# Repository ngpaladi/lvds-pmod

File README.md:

# lvds-pmod
LVDS adapter for PMOD

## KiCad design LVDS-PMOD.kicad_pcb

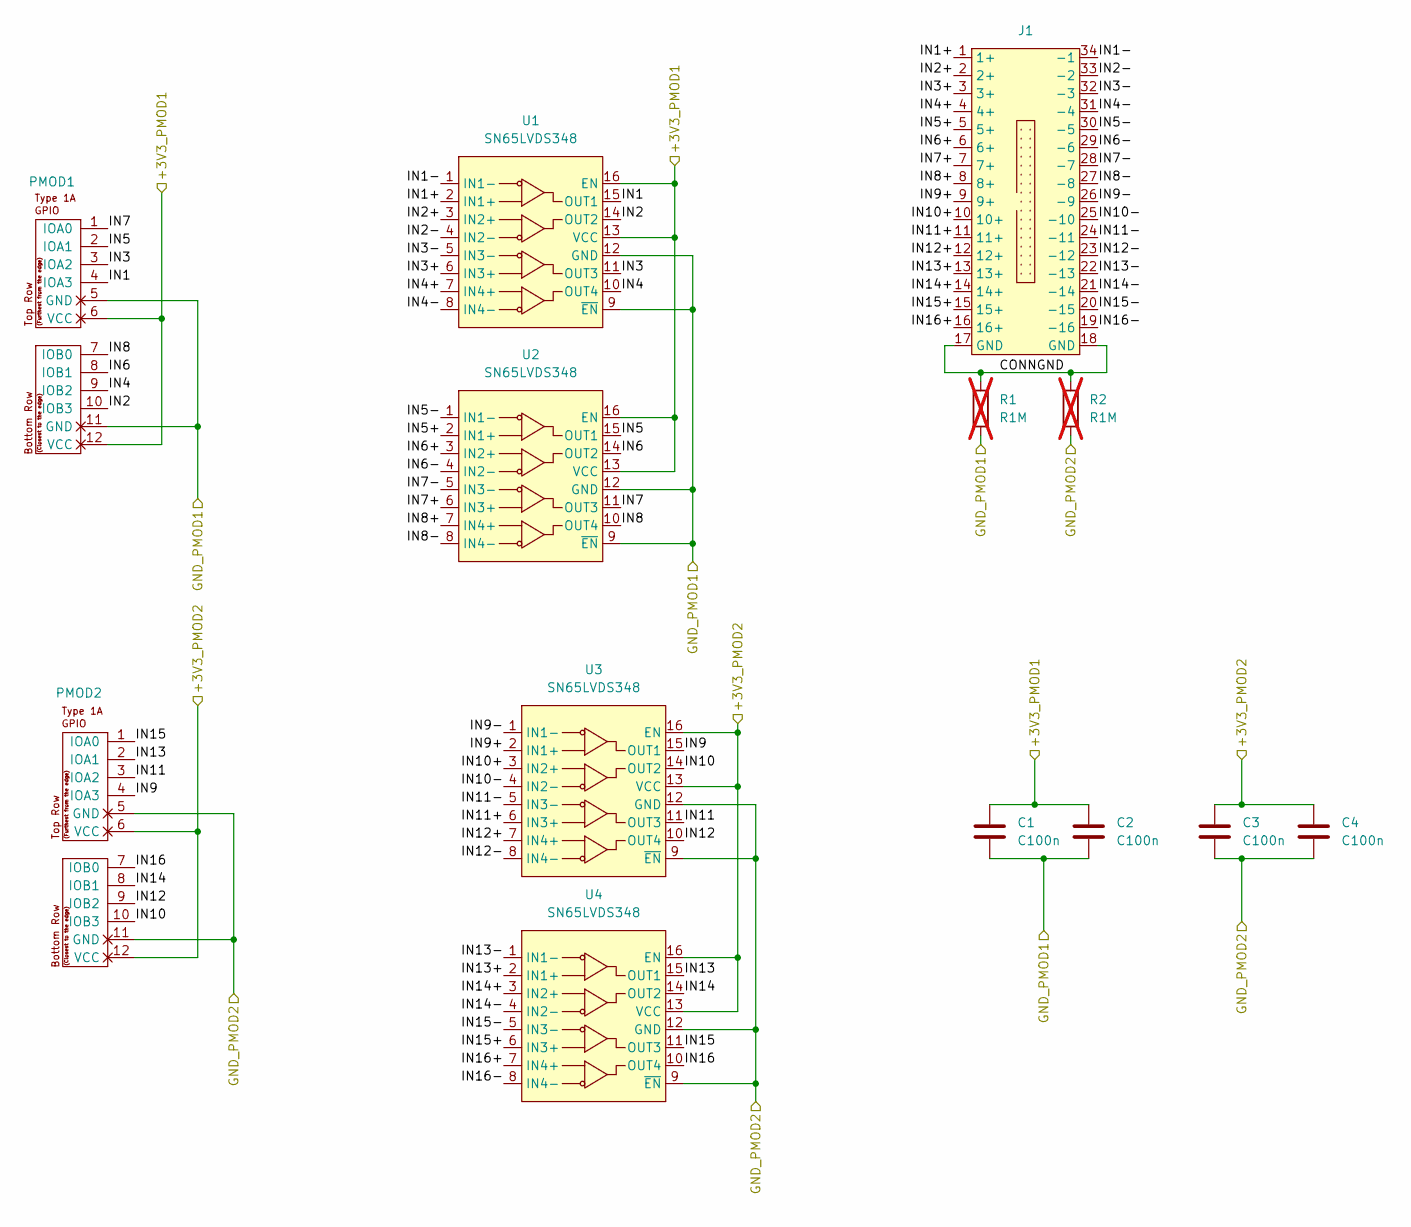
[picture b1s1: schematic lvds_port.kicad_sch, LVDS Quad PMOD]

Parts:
C1, C2, C3, C4: C100n; C_0402_1005Metric_Pad0.74x0.62mm_HandSolder
J1: 302-S341; LVDS_Connector
PMOD1, PMOD2: PMOD-Device-x2-Type-1A-GPIO; pmod_pin_array_6x2
R1, R2: R1M; R_1206_3216Metric_Pad1.30x1.75mm_HandSolder; not fitted
U1, U2, U3, U4: SN65LVDS348; SOIC-16_3.9x9.9mm_P1.27mm

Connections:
+3V3A: C1.1, C2.1, PMOD1.6 (VCC), PMOD1.12 (VCC), U1.13 (VCC), U1.16 (EN), U2.13 (VCC), U2.16 (EN)
+3V3B: C3.1, C4.1, PMOD2.6 (VCC), PMOD2.12 (VCC), U3.13 (VCC), U3.16 (EN), U4.13 (VCC), U4.16 (EN)
/LVDS Port AB/CONNGND: J1.17 (GND), J1.18 (GND), R1.1, R2.1
/LVDS Port AB/IN1: PMOD1.4 (IOA3), U1.15 (OUT1)
/LVDS Port AB/IN1+: J1.1 (1+), U1.2 (IN1+)
/LVDS Port AB/IN1-: J1.34 (-1), U1.1 (IN1-)
/LVDS Port AB/IN2: PMOD1.10 (IOB3), U1.14 (OUT2)
/LVDS Port AB/IN2+: J1.2 (2+), U1.3 (IN2+)
/LVDS Port AB/IN2-: J1.33 (-2), U1.4 (IN2-)
/LVDS Port AB/IN3: PMOD1.3 (IOA2), U1.11 (OUT3)
/LVDS Port AB/IN3+: J1.3 (3+), U1.6 (IN3+)
/LVDS Port AB/IN3-: J1.32 (-3), U1.5 (IN3-)
/LVDS Port AB/IN4: PMOD1.9 (IOB2), U1.10 (OUT4)
/LVDS Port AB/IN4+: J1.4 (4+), U1.7 (IN4+)
/LVDS Port AB/IN4-: J1.31 (-4), U1.8 (IN4-)
/LVDS Port AB/IN5: PMOD1.2 (IOA1), U2.15 (OUT1)
/LVDS Port AB/IN5+: J1.5 (5+), U2.2 (IN1+)
/LVDS Port AB/IN5-: J1.30 (-5), U2.1 (IN1-)
/LVDS Port AB/IN6: PMOD1.8 (IOB1), U2.14 (OUT2)
/LVDS Port AB/IN6+: J1.6 (6+), U2.3 (IN2+)
/LVDS Port AB/IN6-: J1.29 (-6), U2.4 (IN2-)
/LVDS Port AB/IN7: PMOD1.1 (IOA0), U2.11 (OUT3)
/LVDS Port AB/IN7+: J1.7 (7+), U2.6 (IN3+)
/LVDS Port AB/IN7-: J1.28 (-7), U2.5 (IN3-)
/LVDS Port AB/IN8: PMOD1.7 (IOB0), U2.10 (OUT4)
/LVDS Port AB/IN8+: J1.8 (8+), U2.7 (IN4+)
/LVDS Port AB/IN8-: J1.27 (-8), U2.8 (IN4-)
/LVDS Port AB/IN9: PMOD2.4 (IOA3), U3.15 (OUT1)
/LVDS Port AB/IN9+: J1.9 (9+), U3.2 (IN1+)
/LVDS Port AB/IN9-: J1.26 (-9), U3.1 (IN1-)
/LVDS Port AB/IN10: PMOD2.10 (IOB3), U3.14 (OUT2)
/LVDS Port AB/IN10+: J1.10 (10+), U3.3 (IN2+)
/LVDS Port AB/IN10-: J1.25 (-10), U3.4 (IN2-)
/LVDS Port AB/IN11: PMOD2.3 (IOA2), U3.11 (OUT3)
/LVDS Port AB/IN11+: J1.11 (11+), U3.6 (IN3+)
/LVDS Port AB/IN11-: J1.24 (-11), U3.5 (IN3-)
/LVDS Port AB/IN12: PMOD2.9 (IOB2), U3.10 (OUT4)
/LVDS Port AB/IN12+: J1.12 (12+), U3.7 (IN4+)
/LVDS Port AB/IN12-: J1.23 (-12), U3.8 (IN4-)
/LVDS Port AB/IN13: PMOD2.2 (IOA1), U4.15 (OUT1)
/LVDS Port AB/IN13+: J1.13 (13+), U4.2 (IN1+)
/LVDS Port AB/IN13-: J1.22 (-13), U4.1 (IN1-)
/LVDS Port AB/IN14: PMOD2.8 (IOB1), U4.14 (OUT2)
/LVDS Port AB/IN14+: J1.14 (14+), U4.3 (IN2+)
/LVDS Port AB/IN14-: J1.21 (-14), U4.4 (IN2-)
/LVDS Port AB/IN15: PMOD2.1 (IOA0), U4.11 (OUT3)
/LVDS Port AB/IN15+: J1.15 (15+), U4.6 (IN3+)
/LVDS Port AB/IN15-: J1.20 (-15), U4.5 (IN3-)
/LVDS Port AB/IN16: PMOD2.7 (IOB0), U4.10 (OUT4)
/LVDS Port AB/IN16+: J1.16 (16+), U4.7 (IN4+)
/LVDS Port AB/IN16-: J1.19 (-16), U4.8 (IN4-)
GND: C1.2, C2.2, C3.2, C4.2, PMOD1.5 (GND), PMOD1.11 (GND), PMOD2.5 (GND), PMOD2.11 (GND), R1.2, R2.2, U1.9 (~EN), U1.12 (GND), U2.9 (~EN), U2.12 (GND), U3.9 (~EN), U3.12 (GND), U4.9 (~EN), U4.12 (GND); also elsewhere on the board

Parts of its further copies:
C5, C6, C7, C8: C100n; C_0402_1005Metric_Pad0.74x0.62mm_HandSolder
J2: 302-S341; LVDS_Connector
PMOD3, PMOD4: PMOD-Device-x2-Type-1A-GPIO; pmod_pin_array_6x2
R3, R4: R1M; R_1206_3216Metric_Pad1.30x1.75mm_HandSolder; not fitted
U5, U6, U7, U8: SN65LVDS348; SOIC-16_3.9x9.9mm_P1.27mm

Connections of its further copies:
+3V3C: C5.1, C6.1, PMOD3.6 (VCC), PMOD3.12 (VCC), U5.13 (VCC), U5.16 (EN), U6.13 (VCC), U6.16 (EN)
+3V3D: C7.1, C8.1, PMOD4.6 (VCC), PMOD4.12 (VCC), U7.13 (VCC), U7.16 (EN), U8.13 (VCC), U8.16 (EN)
/LVDS Port CD/CONNGND: J2.17 (GND), J2.18 (GND), R3.1, R4.1
/LVDS Port CD/IN1: PMOD3.4 (IOA3), U5.15 (OUT1)
/LVDS Port CD/IN1+: J2.1 (1+), U5.2 (IN1+)
/LVDS Port CD/IN1-: J2.34 (-1), U5.1 (IN1-)
/LVDS Port CD/IN2: PMOD3.10 (IOB3), U5.14 (OUT2)
/LVDS Port CD/IN2+: J2.2 (2+), U5.3 (IN2+)
/LVDS Port CD/IN2-: J2.33 (-2), U5.4 (IN2-)
/LVDS Port CD/IN3: PMOD3.3 (IOA2), U5.11 (OUT3)
/LVDS Port CD/IN3+: J2.3 (3+), U5.6 (IN3+)
/LVDS Port CD/IN3-: J2.32 (-3), U5.5 (IN3-)
/LVDS Port CD/IN4: PMOD3.9 (IOB2), U5.10 (OUT4)
/LVDS Port CD/IN4+: J2.4 (4+), U5.7 (IN4+)
/LVDS Port CD/IN4-: J2.31 (-4), U5.8 (IN4-)
/LVDS Port CD/IN5: PMOD3.2 (IOA1), U6.15 (OUT1)
/LVDS Port CD/IN5+: J2.5 (5+), U6.2 (IN1+)
/LVDS Port CD/IN5-: J2.30 (-5), U6.1 (IN1-)
/LVDS Port CD/IN6: PMOD3.8 (IOB1), U6.14 (OUT2)
/LVDS Port CD/IN6+: J2.6 (6+), U6.3 (IN2+)
/LVDS Port CD/IN6-: J2.29 (-6), U6.4 (IN2-)
/LVDS Port CD/IN7: PMOD3.1 (IOA0), U6.11 (OUT3)
/LVDS Port CD/IN7+: J2.7 (7+), U6.6 (IN3+)
/LVDS Port CD/IN7-: J2.28 (-7), U6.5 (IN3-)
/LVDS Port CD/IN8: PMOD3.7 (IOB0), U6.10 (OUT4)
/LVDS Port CD/IN8+: J2.8 (8+), U6.7 (IN4+)
/LVDS Port CD/IN8-: J2.27 (-8), U6.8 (IN4-)
/LVDS Port CD/IN9: PMOD4.4 (IOA3), U7.15 (OUT1)
/LVDS Port CD/IN9+: J2.9 (9+), U7.2 (IN1+)
/LVDS Port CD/IN9-: J2.26 (-9), U7.1 (IN1-)
/LVDS Port CD/IN10: PMOD4.10 (IOB3), U7.14 (OUT2)
/LVDS Port CD/IN10+: J2.10 (10+), U7.3 (IN2+)
/LVDS Port CD/IN10-: J2.25 (-10), U7.4 (IN2-)
/LVDS Port CD/IN11: PMOD4.3 (IOA2), U7.11 (OUT3)
/LVDS Port CD/IN11+: J2.11 (11+), U7.6 (IN3+)
/LVDS Port CD/IN11-: J2.24 (-11), U7.5 (IN3-)
/LVDS Port CD/IN12: PMOD4.9 (IOB2), U7.10 (OUT4)
/LVDS Port CD/IN12+: J2.12 (12+), U7.7 (IN4+)
/LVDS Port CD/IN12-: J2.23 (-12), U7.8 (IN4-)
/LVDS Port CD/IN13: PMOD4.2 (IOA1), U8.15 (OUT1)
/LVDS Port CD/IN13+: J2.13 (13+), U8.2 (IN1+)
/LVDS Port CD/IN13-: J2.22 (-13), U8.1 (IN1-)
/LVDS Port CD/IN14: PMOD4.8 (IOB1), U8.14 (OUT2)
/LVDS Port CD/IN14+: J2.14 (14+), U8.3 (IN2+)
/LVDS Port CD/IN14-: J2.21 (-14), U8.4 (IN2-)
/LVDS Port CD/IN15: PMOD4.1 (IOA0), U8.11 (OUT3)
/LVDS Port CD/IN15+: J2.15 (15+), U8.6 (IN3+)
/LVDS Port CD/IN15-: J2.20 (-15), U8.5 (IN3-)
/LVDS Port CD/IN16: PMOD4.7 (IOB0), U8.10 (OUT4)
/LVDS Port CD/IN16+: J2.16 (16+), U8.7 (IN4+)
/LVDS Port CD/IN16-: J2.19 (-16), U8.8 (IN4-)
GND: C5.2, C6.2, C7.2, C8.2, PMOD3.5 (GND), PMOD3.11 (GND), PMOD4.5 (GND), PMOD4.11 (GND), R3.2, R4.2, U5.9 (~EN), U5.12 (GND), U6.9 (~EN), U6.12 (GND), U7.9 (~EN), U7.12 (GND), U8.9 (~EN), U8.12 (GND); also elsewhere on the board

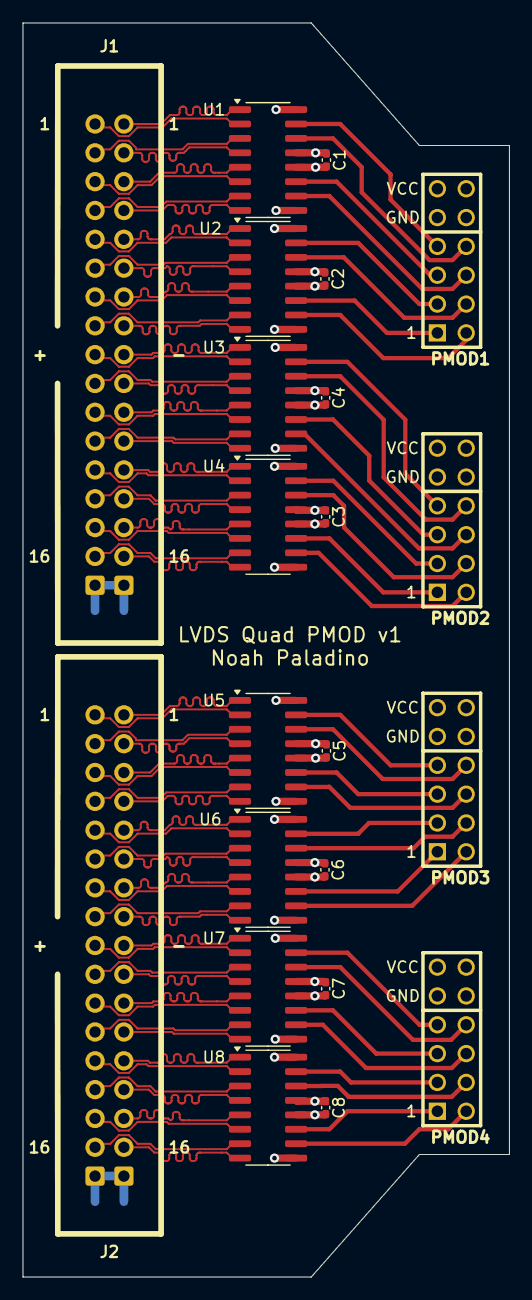
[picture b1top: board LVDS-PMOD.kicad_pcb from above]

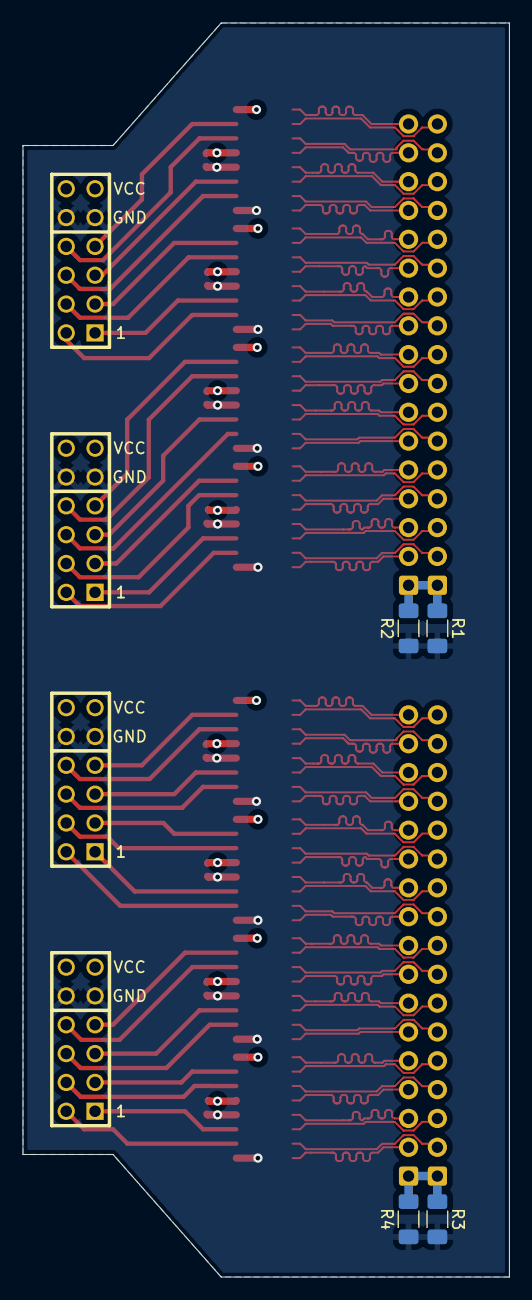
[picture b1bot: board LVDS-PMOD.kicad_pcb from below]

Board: 4 copper layers, 42.9 x 110.5 mm, 26 parts (4 on the bottom side), 103 nets.

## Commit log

2025-03-20 Basic Design
2025-03-21 Add HTML BOM
